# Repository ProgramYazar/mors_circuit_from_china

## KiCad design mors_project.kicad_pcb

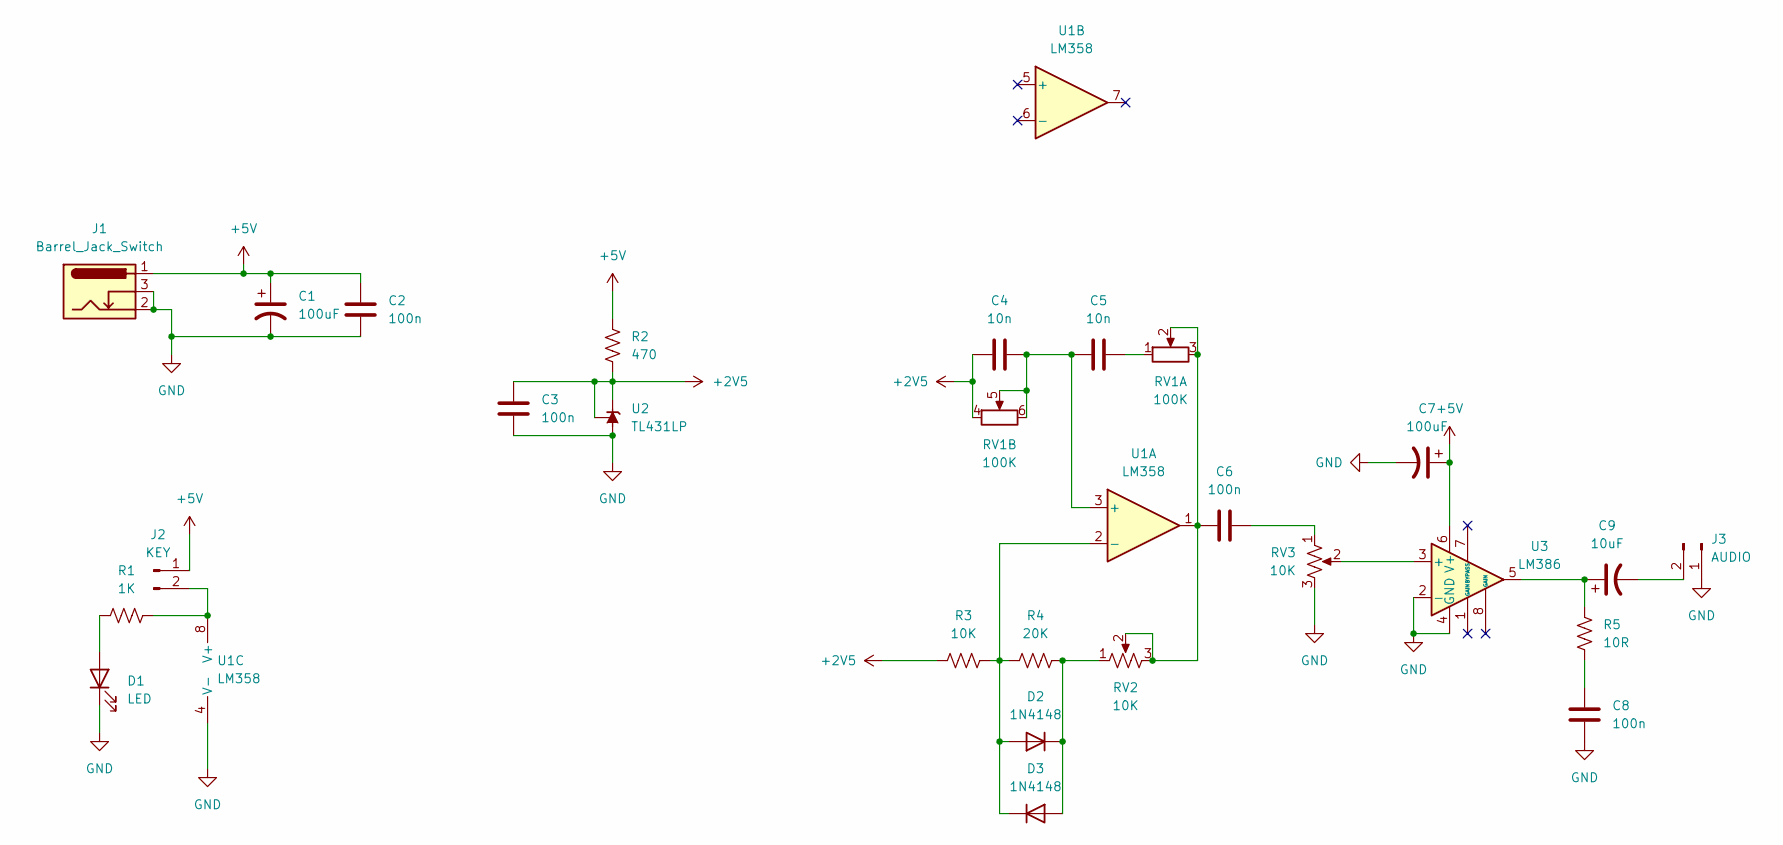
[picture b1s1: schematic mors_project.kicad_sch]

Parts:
C1, C7: 100uF; CP_Radial_D5.0mm_P2.50mm
C2, C3, C6, C8: 100n; C_Disc_D3.0mm_W2.0mm_P2.50mm
C4, C5: 10n; C_Disc_D3.0mm_W2.0mm_P2.50mm
C9: 10uF; CP_Radial_D5.0mm_P2.50mm
D1: LED; LED_D5.0mm_FlatTop
D2, D3: 1N4148; D_DO-35_SOD27_P7.62mm_Horizontal
J1: Barrel_Jack_Switch; BarrelJack_Wuerth_6941xx301002
J2: KEY; PinSocket_1x02_P2.54mm_Vertical
J3: AUDIO; PinSocket_1x02_P2.54mm_Vertical
R1: 1K; R_1206_3216Metric
R2: 470; R_1206_3216Metric
R3: 10K; R_1206_3216Metric
R4: 20K; R_1206_3216Metric
R5: 10R; R_1206_3216Metric
RV1: 100K; Potentiometer_Alps_RK097_Dual_Horizontal
RV2, RV3: 10K; Potentiometer_Alps_RK09Y11_Single_Horizontal
U1: LM358; DIP-8_W7.62mm_LongPads
U2: TL431LP; TO-92_Inline
U3: LM386; DIP-8_W7.62mm_LongPads

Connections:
+2V5: C3.1, C4.1, R2.2, R3.1, RV1.4, U2.1 (REF), U2.3 (K)
+5V: C1.1, C2.1, C7.1, J1.1, J2.1, R2.1, U3.6 (V+)
GND: C1.2, C2.2, C3.2, C7.2, C8.1, D1.1 (K), J1.2, J1.3, J3.1, RV3.3, U1.4 (V-), U2.2 (A), U3.2 (-), U3.4 (GND)
unnamed: C4.2, C5.1, RV1.5, RV1.6, U1.3 (+)
unnamed: C5.2, RV1.1
unnamed: C6.1, RV1.2, RV1.3, RV2.2, RV2.3, U1.1
unnamed: C6.2, RV3.1
unnamed: C8.2, R5.1
unnamed: C9.1, R5.2, U3.5
unnamed: C9.2, J3.2
unnamed: D1.2 (A), R1.1
unnamed: D2.1 (K), D3.2 (A), R4.2, RV2.1
unnamed: D2.2 (A), D3.1 (K), R3.2, R4.1, U1.2 (-)
unnamed: J2.2, R1.2, U1.8 (V+)
unnamed: RV3.2, U3.3 (+)

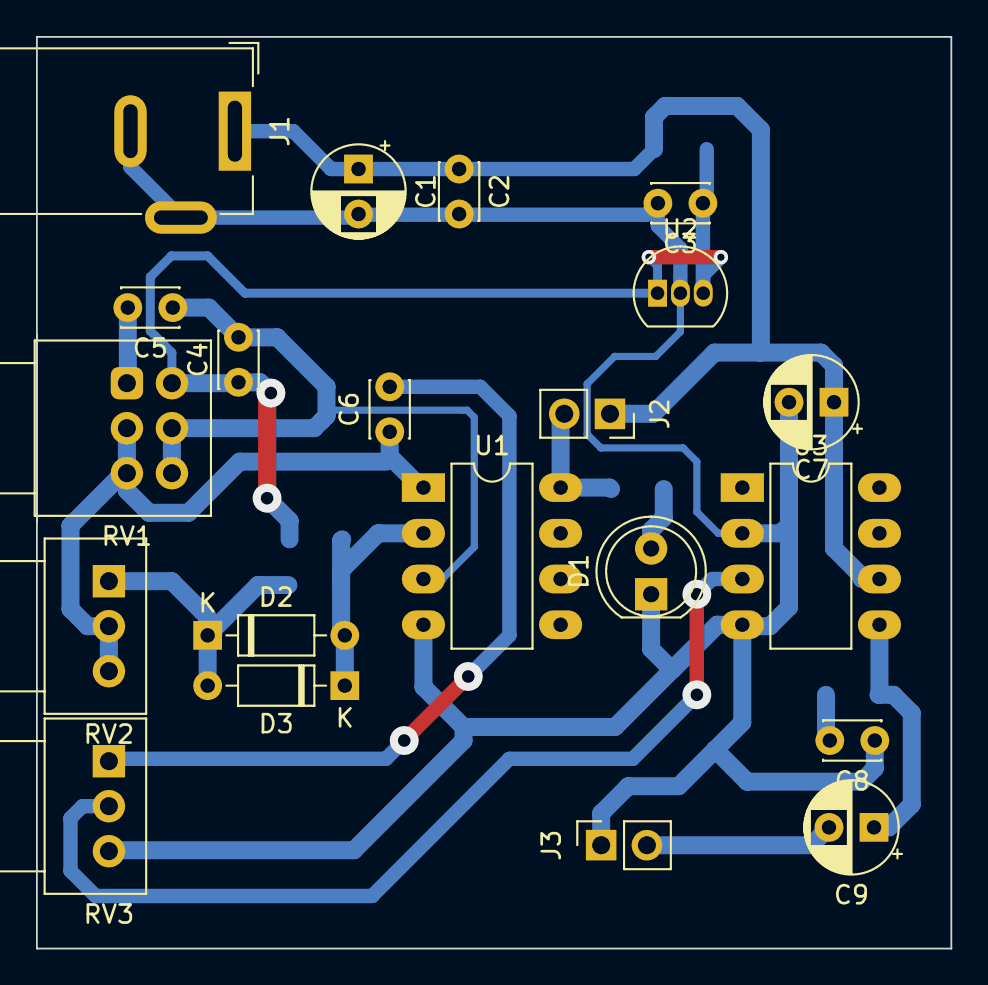
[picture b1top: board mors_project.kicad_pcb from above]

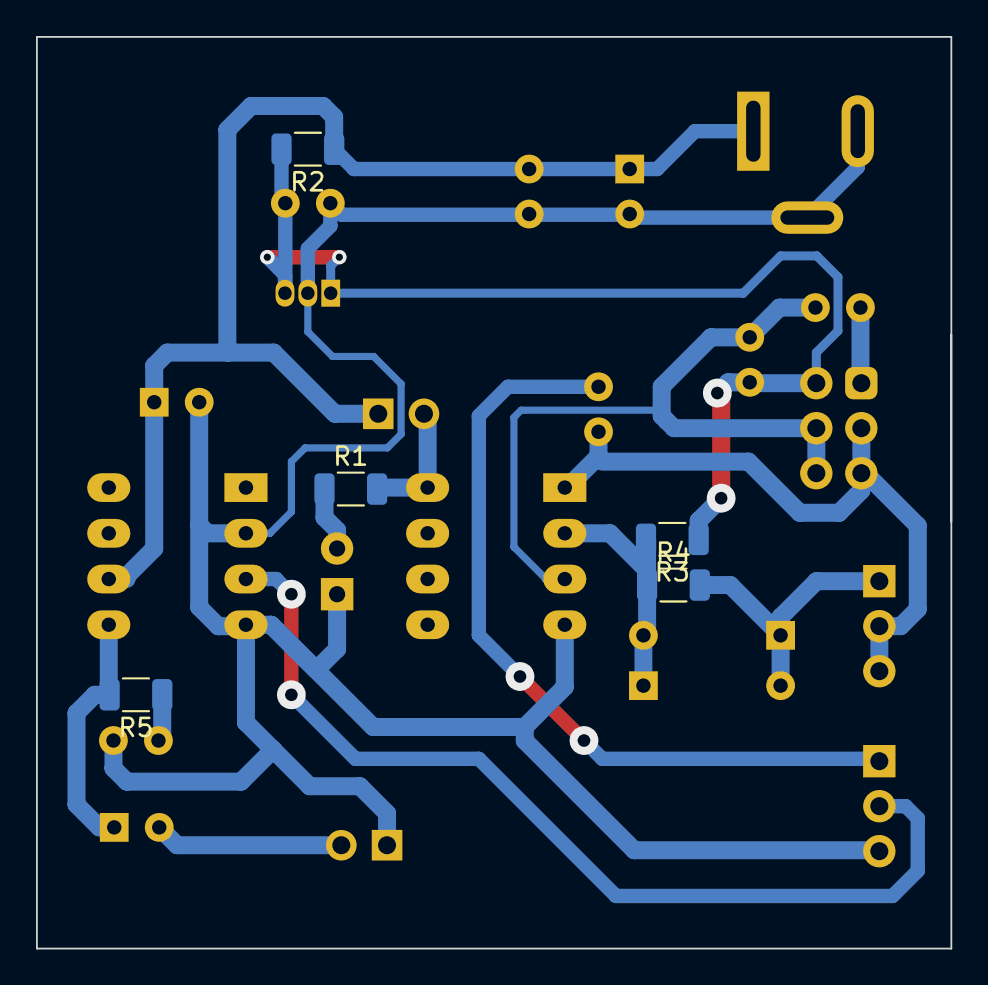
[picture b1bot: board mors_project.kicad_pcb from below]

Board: 2 copper layers, 50.8 x 50.6 mm, 26 parts (5 on the bottom side), 15 nets.

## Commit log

2022-08-07 Add files via upload
    cw practice pcb (steal from chine) created by Kicad
